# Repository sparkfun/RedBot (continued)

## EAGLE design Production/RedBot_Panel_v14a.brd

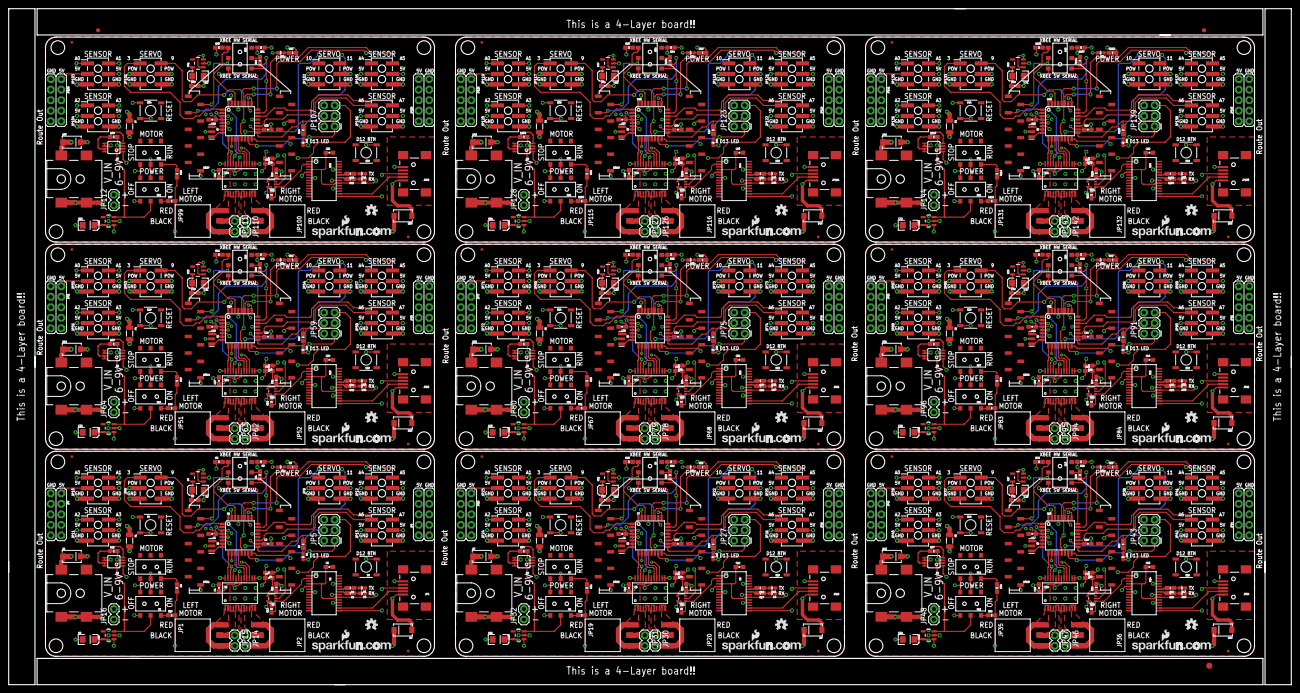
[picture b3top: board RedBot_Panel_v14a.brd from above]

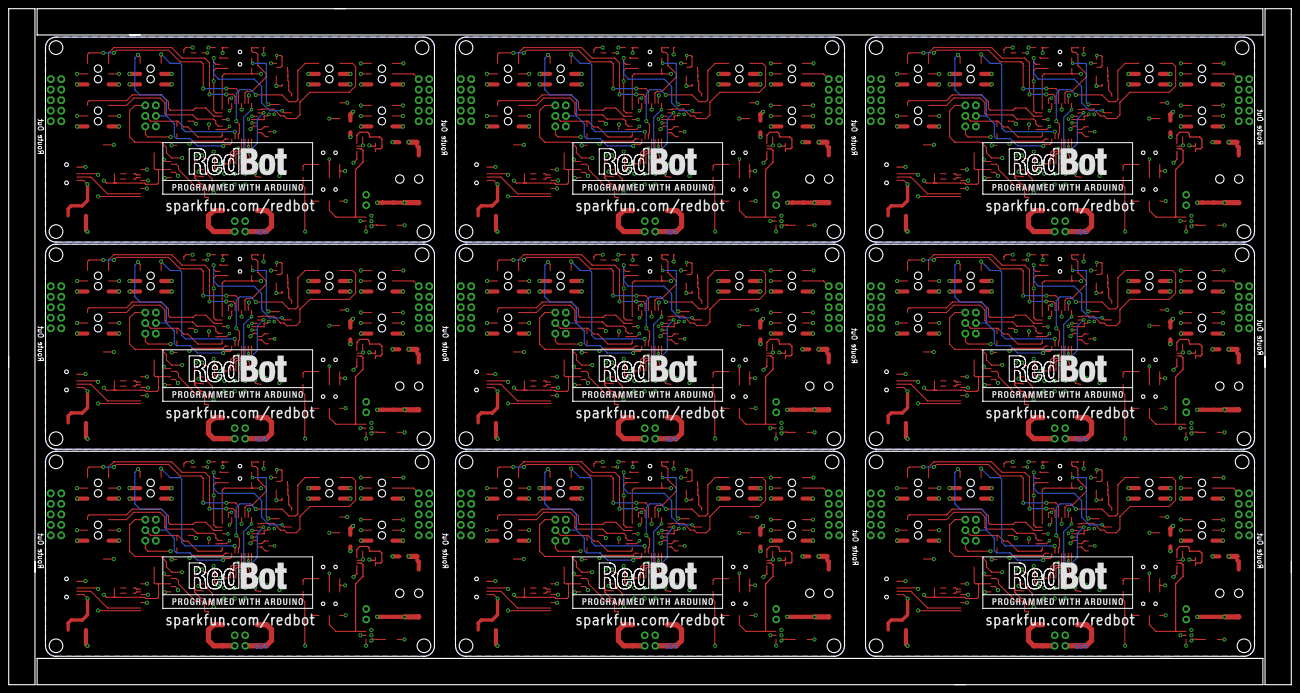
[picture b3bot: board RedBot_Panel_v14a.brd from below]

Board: 4 copper layers, 309.9 x 163.3 mm, 606 parts (9 on the bottom side), 531 nets.

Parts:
C1, C2, C3, C4, C5, C6, C7, C10, C11, C12, C13, C14, C17, C18, C19, C20, C21, C22, C25, C26, C27, C28, C29, C30, C33, C34, C35, C36, C37, C38, C41, C42, C43, C44, C45, C46, C49, C50, C51, C52, C53, C54, C57, C58, C59, C60, C61, C62, C65, C66, C67, C68, C69, C70: 0.1uF; 0603-CAP
C8, C9, C15, C16, C23, C24, C31, C32, C39, C40, C47, C48, C55, C56, C63, C64, C71, C72: 10uF; EIA3216
D1, D2, D7, D8, D13, D14, D19, D20, D25, D26, D31, D32, D37, D38, D43, D44, D49, D50: SMA-DIODE
D3, D4, D5, D6, D9, D10, D11, D12, D15, D16, D17, D18, D21, D22, D23, D24, D27, D28, D29, D30, D33, D34, D35, D36, D39, D40, D41, D42, D45, D46, D47, D48, D51, D52, D53, D54: GREEN; LED-0603
E$1: FIDUCIAL-1.5X3
E$7, E$8: FIDUCIAL-1X2
F1, F2, F3, F4, F5, F6, F7, F8, F9: PTCSMD; PTC-1206
FID1, FID2, FID3, FID4, FID5, FID6, FID7, FID8, FID9, FID10, FID11, FID12, FID13, FID14, FID15, FID16, FID17, FID18: FIDUCIALUFIDUCIAL; MICRO-FIDUCIAL
JP1, JP2, JP19, JP20, JP35, JP36, JP51, JP52, JP67, JP68, JP83, JP84, JP99, JP100, JP115, JP116, JP131, JP132: 1x3 RA Female .1"; 1X03_SMD_RA_FEMALE
JP3, JP17, JP33, JP49, JP65, JP81, JP97, JP113, JP129: 5.5x2.1mm Barrel; POWER_JACK_SMD
JP4, JP18, JP34, JP50, JP66, JP82, JP98, JP114, JP130: USB-B; USB-MINIB
JP5, JP27, JP43, JP59, JP75, JP91, JP107, JP123, JP139: AVR_SPI_PRG_6PTH; 2X3
JP6, JP7, JP28, JP29, JP44, JP45, JP60, JP61, JP76, JP77, JP92, JP93, JP108, JP109, JP124, JP125, JP140, JP141: M05X2NO_SILK; 2X5_NOSILK
JP8, JP9, JP10, JP11, JP12, JP13, JP21, JP22, JP23, JP24, JP25, JP26, JP37, JP38, JP39, JP40, JP41, JP42, JP53, JP54, JP55, JP56, JP57, JP58, JP69, JP70, JP71, JP72, JP73, JP74, JP85, JP86, JP87, JP88, JP89, JP90, JP101, JP102, JP103, JP104, JP105, JP106, JP117, JP118, JP119, JP120, JP121, JP122, JP133, JP134, JP135, JP136, JP137, JP138: 2X3_SMT_POSTS
JP14, JP15, JP16, JP30, JP31, JP32, JP46, JP47, JP48, JP62, JP63, JP64, JP78, JP79, JP80, JP94, JP95, JP96, JP110, JP111, JP112, JP126, JP127, JP128, JP142, JP143, JP144: 1X02
MOD1, MOD2, MOD3, MOD4, MOD5, MOD6, MOD7, MOD8, MOD9: XBEE-1B3; XBEE-SMD
Q1, Q2, Q3, Q4, Q5, Q6, Q7, Q8, Q9: MSOP8
R1, R9, R10, R11, R12, R13, R14, R21, R22, R24, R25, R26, R27, R34, R35, R37, R38, R39, R40, R47, R48, R50, R51, R52, R53, R60, R61, R63, R64, R65, R66, R73, R74, R76, R77, R78, R79, R86, R87, R89, R90, R91, R92, R99, R100, R102, R103, R104, R105, R112, R113, R115, R116, R117: 10k; 0603-RES
R2, R3, R4, R5, R6, R7, R8, R15, R16, R17, R18, R19, R20, R23, R28, R29, R30, R31, R32, R33, R36, R41, R42, R43, R44, R45, R46, R49, R54, R55, R56, R57, R58, R59, R62, R67, R68, R69, R70, R71, R72, R75, R80, R81, R82, R83, R84, R85, R88, R93, R94, R95, R96, R97, R98, R101, R106, R107, R108, R109, R110, R111, R114: 1k; 0603-RES
S1, S2, S3, S6, S7, S8, S11, S12, S13, S16, S17, S18, S21, S22, S23, S26, S27, S28, S31, S32, S33, S36, S37, S38, S41, S42, S43: DPDT; AYZ0202
S4, S5, S9, S10, S14, S15, S19, S20, S24, S25, S29, S30, S34, S35, S39, S40, S44, S45: TACTILE_SWITCH_SMD
SFE-LOGO1, SFE-LOGO2, SFE-LOGO3, SFE-LOGO4, SFE-LOGO5, SFE-LOGO6, SFE-LOGO7, SFE-LOGO8, SFE-LOGO9: LOGO-SFENEW; SFE-NEW-WEBLOGO
STANDOFF1, STANDOFF2, STANDOFF3, STANDOFF4, STANDOFF5, STANDOFF6, STANDOFF7, STANDOFF8, STANDOFF9, STANDOFF10, STANDOFF11, STANDOFF12, STANDOFF13, STANDOFF14, STANDOFF15, STANDOFF16, STANDOFF17, STANDOFF18, STANDOFF19, STANDOFF20, STANDOFF21, STANDOFF22, STANDOFF23, STANDOFF24, STANDOFF25, STANDOFF26, STANDOFF27, STANDOFF28, STANDOFF29, STANDOFF30, STANDOFF31, STANDOFF32, STANDOFF33, STANDOFF34, STANDOFF35, STANDOFF36: STAND-OFF
U1, U7, U13, U19, U25, U31, U37, U43, U49: ATMEGA328P; TQFP32-08
U2, U9, U15, U21, U27, U33, U39, U45, U51: TB6612FNG; SSOP24
U3, U10, U16, U22, U28, U34, U40, U46, U52: MIC5219 5V; SOT23-5
U4, U11, U17, U23, U29, U35, U41, U47, U53: MIC5219 3.3V; SOT23-5
U5, U8, U14, U20, U26, U32, U38, U44, U50: FT232RLSSOP; SSOP28DB
U6, U12, U18, U24, U30, U36, U42, U48, U54: 7408SE; SOT353
U$1, U$3, U$5, U$7, U$9, U$11, U$13, U$15, U$17: OSHW-LOGOS; OSHW-LOGO-S
U$2, U$4, U$6, U$8, U$10, U$12, U$14, U$16, U$23: REDBOT_LOGO
Y1, Y2, Y3, Y4, Y5, Y6, Y7, Y8, Y9: 16MHz; RESONATOR-SMD

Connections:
3.3V: C6.1, C8.A, MOD1.1, U4.5
3.3V1: C13.1, C15.A, MOD2.1, U11.5
3.3V2: C21.1, C23.A, MOD3.1, U17.5
3.3V3: C29.1, C31.A, MOD4.1, U23.5
3.3V4: C37.1, C39.A, MOD5.1, U29.5
3.3V5: C45.1, C47.A, MOD6.1, U35.5
3.3V6: C53.1, C55.A, MOD7.1, U41.5
3.3V7: C61.1, C63.A, MOD8.1, U47.5
3.3V8: C69.1, C71.A, MOD9.1, U53.5
5V: C2.1, C3.1, C4.1, C9.A, JP5.2, JP6.1, JP6.3, JP6.5, JP6.7, JP6.9, JP7.1, JP7.3, JP7.5, JP7.7, JP7.9, JP10.3, JP10.4, JP11.3, JP11.4, JP12.3, JP12.4, JP13.3, JP13.4, R1.1, R8.2, R12.2, R13.2, U1.4, U1.6, U1.18, U2.20, U3.5, U4.1, U4.3, U6.5
5V1: C1.1, C10.1, C11.1, C16.A, JP23.3, JP23.4, JP24.3, JP24.4, JP25.3, JP25.4, JP26.3, JP26.4, JP27.2, JP28.1, JP28.3, JP28.5, JP28.7, JP28.9, JP29.1, JP29.3, JP29.5, JP29.7, JP29.9, R14.1, R20.2, R25.2, R26.2, U7.4, U7.6, U7.18, U9.20, U10.5, U11.1, U11.3, U12.5
5V2: C17.1, C18.1, C19.1, C24.A, JP39.3, JP39.4, JP40.3, JP40.4, JP41.3, JP41.4, JP42.3, JP42.4, JP43.2, JP44.1, JP44.3, JP44.5, JP44.7, JP44.9, JP45.1, JP45.3, JP45.5, JP45.7, JP45.9, R27.1, R33.2, R38.2, R39.2, U13.4, U13.6, U13.18, U15.20, U16.5, U17.1, U17.3, U18.5
5V3: C25.1, C26.1, C27.1, C32.A, JP55.3, JP55.4, JP56.3, JP56.4, JP57.3, JP57.4, JP58.3, JP58.4, JP59.2, JP60.1, JP60.3, JP60.5, JP60.7, JP60.9, JP61.1, JP61.3, JP61.5, JP61.7, JP61.9, R40.1, R46.2, R51.2, R52.2, U19.4, U19.6, U19.18, U21.20, U22.5, U23.1, U23.3, U24.5
5V4: C33.1, C34.1, C35.1, C40.A, JP71.3, JP71.4, JP72.3, JP72.4, JP73.3, JP73.4, JP74.3, JP74.4, JP75.2, JP76.1, JP76.3, JP76.5, JP76.7, JP76.9, JP77.1, JP77.3, JP77.5, JP77.7, JP77.9, R53.1, R59.2, R64.2, R65.2, U25.4, U25.6, U25.18, U27.20, U28.5, U29.1, U29.3, U30.5
5V5: C41.1, C42.1, C43.1, C48.A, JP87.3, JP87.4, JP88.3, JP88.4, JP89.3, JP89.4, JP90.3, JP90.4, JP91.2, JP92.1, JP92.3, JP92.5, JP92.7, JP92.9, JP93.1, JP93.3, JP93.5, JP93.7, JP93.9, R66.1, R72.2, R77.2, R78.2, U31.4, U31.6, U31.18, U33.20, U34.5, U35.1, U35.3, U36.5
5V6: C49.1, C50.1, C51.1, C56.A, JP103.3, JP103.4, JP104.3, JP104.4, JP105.3, JP105.4, JP106.3, JP106.4, JP107.2, JP108.1, JP108.3, JP108.5, JP108.7, JP108.9, JP109.1, JP109.3, JP109.5, JP109.7, JP109.9, R79.1, R85.2, R90.2, R91.2, U37.4, U37.6, U37.18, U39.20, U40.5, U41.1, U41.3, U42.5
5V7: C57.1, C58.1, C59.1, C64.A, JP119.3, JP119.4, JP120.3, JP120.4, JP121.3, JP121.4, JP122.3, JP122.4, JP123.2, JP124.1, JP124.3, JP124.5, JP124.7, JP124.9, JP125.1, JP125.3, JP125.5, JP125.7, JP125.9, R92.1, R98.2, R103.2, R104.2, U43.4, U43.6, U43.18, U45.20, U46.5, U47.1, U47.3, U48.5
5V8: C65.1, C66.1, C67.1, C72.A, JP135.3, JP135.4, JP136.3, JP136.4, JP137.3, JP137.4, JP138.3, JP138.4, JP139.2, JP140.1, JP140.3, JP140.5, JP140.7, JP140.9, JP141.1, JP141.3, JP141.5, JP141.7, JP141.9, R105.1, R111.2, R116.2, R117.2, U49.4, U49.6, U49.18, U51.20, U52.5, U53.1, U53.3, U54.5
FT232_RXI: R3.1, U5.5
FT232_RXI1: R16.1, U8.5
FT232_RXI2: R29.1, U14.5
FT232_RXI3: R42.1, U20.5
FT232_RXI4: R55.1, U26.5
FT232_RXI5: R68.1, U32.5
FT232_RXI6: R81.1, U38.5
FT232_RXI7: R94.1, U44.5
FT232_RXI8: R107.1, U50.5
FT232_TXO: R2.1, U5.1
FT232_TXO1: R15.1, U8.1
FT232_TXO2: R28.1, U14.1
FT232_TXO3: R41.1, U20.1
FT232_TXO4: R54.1, U26.1
FT232_TXO5: R67.1, U32.1
FT232_TXO6: R80.1, U38.1
FT232_TXO7: R93.1, U44.1
FT232_TXO8: R106.1, U50.1
FTDI_DTR: R13.1, U5.2, U6.1
FTDI_DTR1: R26.1, U8.2, U12.1
FTDI_DTR2: R39.1, U14.2, U18.1
FTDI_DTR3: R52.1, U20.2, U24.1
FTDI_DTR4: R65.1, U26.2, U30.1
FTDI_DTR5: R78.1, U32.2, U36.1
FTDI_DTR6: R91.1, U38.2, U42.1
FTDI_DTR7: R104.1, U44.2, U48.1
FTDI_DTR8: R117.1, U50.2, U54.1
GND: C2.2, C3.2, C4.2, C5.2, C6.2, C8.C, C9.C, D4.C, D6.C, JP3.GND, JP3.P$4, JP4.GND, JP5.6, JP6.2, JP6.4, JP6.6, JP6.8, JP6.10, JP7.2, JP7.4, JP7.6, JP7.8, JP7.10, JP8.5, JP8.6, JP9.5, JP9.6, JP10.5, JP10.6, JP11.5, JP11.6, JP12.5, JP12.6, JP13.5, JP13.6, JP16.1, MOD1.10, Q1.1, S1.3, S1.6, S2.3, S4.1, S5.1, U1.3, U1.5, U1.21, U2.3, U2.4, U2.9, U2.10, U2.18, U3.2, U4.2, U5.7, U5.18, U5.21, U5.25, U5.26, U6.3, Y1.2
GND1: C1.2, C10.2, C11.2, C12.2, C13.2, C15.C, C16.C, D10.C, D12.C, JP17.GND, JP17.P$4, JP18.GND, JP21.5, JP21.6, JP22.5, JP22.6, JP23.5, JP23.6, JP24.5, JP24.6, JP25.5, JP25.6, JP26.5, JP26.6, JP27.6, JP28.2, JP28.4, JP28.6, JP28.8, JP28.10, JP29.2, JP29.4, JP29.6, JP29.8, JP29.10, JP32.1, MOD2.10, Q2.1, S6.3, S6.6, S7.3, S9.1, S10.1, U7.3, U7.5, U7.21, U8.7, U8.18, U8.21, U8.25, U8.26, U9.3, U9.4, U9.9, U9.10, U9.18, U10.2, U11.2, U12.3, Y2.2
GND2: C17.2, C18.2, C19.2, C20.2, C21.2, C23.C, C24.C, D16.C, D18.C, JP33.GND, JP33.P$4, JP34.GND, JP37.5, JP37.6, JP38.5, JP38.6, JP39.5, JP39.6, JP40.5, JP40.6, JP41.5, JP41.6, JP42.5, JP42.6, JP43.6, JP44.2, JP44.4, JP44.6, JP44.8, JP44.10, JP45.2, JP45.4, JP45.6, JP45.8, JP45.10, JP48.1, MOD3.10, Q3.1, S11.3, S11.6, S12.3, S14.1, S15.1, U13.3, U13.5, U13.21, U14.7, U14.18, U14.21, U14.25, U14.26, U15.3, U15.4, U15.9, U15.10, U15.18, U16.2, U17.2, U18.3, Y3.2
GND3: C25.2, C26.2, C27.2, C28.2, C29.2, C31.C, C32.C, D22.C, D24.C, JP49.GND, JP49.P$4, JP50.GND, JP53.5, JP53.6, JP54.5, JP54.6, JP55.5, JP55.6, JP56.5, JP56.6, JP57.5, JP57.6, JP58.5, JP58.6, JP59.6, JP60.2, JP60.4, JP60.6, JP60.8, JP60.10, JP61.2, JP61.4, JP61.6, JP61.8, JP61.10, JP64.1, MOD4.10, Q4.1, S16.3, S16.6, S17.3, S19.1, S20.1, U19.3, U19.5, U19.21, U20.7, U20.18, U20.21, U20.25, U20.26, U21.3, U21.4, U21.9, U21.10, U21.18, U22.2, U23.2, U24.3, Y4.2
GND4: C33.2, C34.2, C35.2, C36.2, C37.2, C39.C, C40.C, D28.C, D30.C, JP65.GND, JP65.P$4, JP66.GND, JP69.5, JP69.6, JP70.5, JP70.6, JP71.5, JP71.6, JP72.5, JP72.6, JP73.5, JP73.6, JP74.5, JP74.6, JP75.6, JP76.2, JP76.4, JP76.6, JP76.8, JP76.10, JP77.2, JP77.4, JP77.6, JP77.8, JP77.10, JP80.1, MOD5.10, Q5.1, S21.3, S21.6, S22.3, S24.1, S25.1, U25.3, U25.5, U25.21, U26.7, U26.18, U26.21, U26.25, U26.26, U27.3, U27.4, U27.9, U27.10, U27.18, U28.2, U29.2, U30.3, Y5.2
GND5: C41.2, C42.2, C43.2, C44.2, C45.2, C47.C, C48.C, D34.C, D36.C, JP81.GND, JP81.P$4, JP82.GND, JP85.5, JP85.6, JP86.5, JP86.6, JP87.5, JP87.6, JP88.5, JP88.6, JP89.5, JP89.6, JP90.5, JP90.6, JP91.6, JP92.2, JP92.4, JP92.6, JP92.8, JP92.10, JP93.2, JP93.4, JP93.6, JP93.8, JP93.10, JP96.1, MOD6.10, Q6.1, S26.3, S26.6, S27.3, S29.1, S30.1, U31.3, U31.5, U31.21, U32.7, U32.18, U32.21, U32.25, U32.26, U33.3, U33.4, U33.9, U33.10, U33.18, U34.2, U35.2, U36.3, Y6.2
GND6: C49.2, C50.2, C51.2, C52.2, C53.2, C55.C, C56.C, D40.C, D42.C, JP97.GND, JP97.P$4, JP98.GND, JP101.5, JP101.6, JP102.5, JP102.6, JP103.5, JP103.6, JP104.5, JP104.6, JP105.5, JP105.6, JP106.5, JP106.6, JP107.6, JP108.2, JP108.4, JP108.6, JP108.8, JP108.10, JP109.2, JP109.4, JP109.6, JP109.8, JP109.10, JP112.1, MOD7.10, Q7.1, S31.3, S31.6, S32.3, S34.1, S35.1, U37.3, U37.5, U37.21, U38.7, U38.18, U38.21, U38.25, U38.26, U39.3, U39.4, U39.9, U39.10, U39.18, U40.2, U41.2, U42.3, Y7.2
GND7: C57.2, C58.2, C59.2, C60.2, C61.2, C63.C, C64.C, D46.C, D48.C, JP113.GND, JP113.P$4, JP114.GND, JP117.5, JP117.6, JP118.5, JP118.6, JP119.5, JP119.6, JP120.5, JP120.6, JP121.5, JP121.6, JP122.5, JP122.6, JP123.6, JP124.2, JP124.4, JP124.6, JP124.8, JP124.10, JP125.2, JP125.4, JP125.6, JP125.8, JP125.10, JP128.1, MOD8.10, Q8.1, S36.3, S36.6, S37.3, S39.1, S40.1, U43.3, U43.5, U43.21, U44.7, U44.18, U44.21, U44.25, U44.26, U45.3, U45.4, U45.9, U45.10, U45.18, U46.2, U47.2, U48.3, Y8.2
GND8: C65.2, C66.2, C67.2, C68.2, C69.2, C71.C, C72.C, D52.C, D54.C, JP129.GND, JP129.P$4, JP130.GND, JP133.5, JP133.6, JP134.5, JP134.6, JP135.5, JP135.6, JP136.5, JP136.6, JP137.5, JP137.6, JP138.5, JP138.6, JP139.6, JP140.2, JP140.4, JP140.6, JP140.8, JP140.10, JP141.2, JP141.4, JP141.6, JP141.8, JP141.10, JP144.1, MOD9.10, Q9.1, S41.3, S41.6, S42.3, S44.1, S45.1, U49.3, U49.5, U49.21, U50.7, U50.18, U50.21, U50.25, U50.26, U51.3, U51.4, U51.9, U51.10, U51.18, U52.2, U53.2, U54.3, Y9.2
L01: JP1.1, JP1.3, JP15.2, U2.1, U2.2
L02: JP1.2, JP15.1, U2.5, U2.6
L03: JP19.1, JP19.3, JP31.2, U9.1, U9.2
L04: JP19.2, JP31.1, U9.5, U9.6
L05: JP35.1, JP35.3, JP47.2, U15.1, U15.2
L06: JP35.2, JP47.1, U15.5, U15.6
L07: JP51.1, JP51.3, JP63.2, U21.1, U21.2
L08: JP51.2, JP63.1, U21.5, U21.6
L09: JP67.1, JP67.3, JP79.2, U27.1, U27.2
L10: JP67.2, JP79.1, U27.5, U27.6
L11: JP83.1, JP83.3, JP95.2, U33.1, U33.2
L12: JP83.2, JP95.1, U33.5, U33.6
L13: JP99.1, JP99.3, JP111.2, U39.1, U39.2
L14: JP99.2, JP111.1, U39.5, U39.6
L15: JP115.1, JP115.3, JP127.2, U45.1, U45.2
L16: JP115.2, JP127.1, U45.5, U45.6
L17: JP131.1, JP131.3, JP143.2, U51.1, U51.2
L18: JP131.2, JP143.1, U51.5, U51.6
L_CTRL_1: U1.32, U2.21
L_CTRL_2: U1.2, U2.22
L_CTRL_3: U7.2, U9.22
L_CTRL_4: U7.32, U9.21
L_CTRL_5: U13.2, U15.22
L_CTRL_6: U13.32, U15.21
L_CTRL_7: U19.2, U21.22
L_CTRL_8: U19.32, U21.21
L_CTRL_9: U25.2, U27.22
L_CTRL_10: U25.32, U27.21
L_CTRL_11: U31.2, U33.22
L_CTRL_12: U31.32, U33.21
L_CTRL_13: U37.2, U39.22
L_CTRL_14: U37.32, U39.21
L_CTRL_15: U43.2, U45.22
L_CTRL_16: U43.32, U45.21
L_CTRL_17: U49.2, U51.22
L_CTRL_18: U49.32, U51.21
MISO: JP5.1, S5.3, U1.16
MISO1: JP27.1, S10.3, U7.16
MISO2: JP43.1, S15.3, U13.16
MISO3: JP59.1, S20.3, U19.16
MISO4: JP75.1, S25.3, U25.16
MISO5: JP91.1, S30.3, U31.16
MISO6: JP107.1, S35.3, U37.16
MISO7: JP123.1, S40.3, U43.16
MISO8: JP139.1, S45.3, U49.16
MOTOR_ENABLE: S1.5, S2.2, U2.19
MOTOR_ENABLE1: S6.5, S7.2, U9.19
MOTOR_ENABLE2: S11.5, S12.2, U15.19
MOTOR_ENABLE3: S16.5, S17.2, U21.19
MOTOR_ENABLE4: S21.5, S22.2, U27.19
MOTOR_ENABLE5: S26.5, S27.2, U33.19
MOTOR_ENABLE6: S31.5, S32.2, U39.19
MOTOR_ENABLE7: S36.5, S37.2, U45.19
MOTOR_ENABLE8: S41.5, S42.2, U51.19
unnamed: R4.2, S3.2
unnamed: Q1.4, Q1.7, Q1.8, R11.1
unnamed: D5.C, R6.1
unnamed: D3.C, R5.1
unnamed: C7.2, U6.4
unnamed: JP4.MTN1, JP4.MTN2, JP4.MTN3, JP4.MTN4
unnamed: D4.A, R7.1
unnamed: D6.A, R8.1
unnamed: F1.2, Q1.5, Q1.6
unnamed: JP18.D-, U8.16
unnamed: JP18.D+, U8.15
unnamed: U7.8, Y2.3
unnamed: U7.7, Y2.1
unnamed: D10.A, R19.1
unnamed: D12.A, R20.1
unnamed: R21.1, S7.1
unnamed: C14.2, U12.4
unnamed: R9.1, S2.1
unnamed: R23.2, S8.2
unnamed: JP18.MTN1, JP18.MTN2, JP18.MTN3, JP18.MTN4
unnamed: Q2.4, Q2.7, Q2.8, R24.1
unnamed: D11.C, R18.1
unnamed: U1.8, Y1.3
unnamed: U1.7, Y1.1
unnamed: D9.C, R17.1
unnamed: JP4.D-, U5.16
unnamed: JP4.D+, U5.15
unnamed: F2.2, Q2.5, Q2.6
unnamed: JP34.D-, U14.16
unnamed: JP34.D+, U14.15
unnamed: U13.8, Y3.3
unnamed: U13.7, Y3.1
unnamed: D16.A, R32.1
unnamed: D18.A, R33.1
unnamed: R34.1, S12.1
unnamed: C22.2, U18.4
unnamed: R36.2, S13.2
unnamed: JP34.MTN1, JP34.MTN2, JP34.MTN3, JP34.MTN4
unnamed: Q3.4, Q3.7, Q3.8, R37.1
unnamed: D17.C, R31.1
unnamed: D15.C, R30.1
unnamed: F3.2, Q3.5, Q3.6
unnamed: JP50.D-, U20.16
unnamed: JP50.D+, U20.15
unnamed: U19.8, Y4.3
unnamed: U19.7, Y4.1
unnamed: D22.A, R45.1
unnamed: D24.A, R46.1
unnamed: R47.1, S17.1
unnamed: C30.2, U24.4
unnamed: R49.2, S18.2
unnamed: JP50.MTN1, JP50.MTN2, JP50.MTN3, JP50.MTN4
unnamed: Q4.4, Q4.7, Q4.8, R50.1
unnamed: D23.C, R44.1
unnamed: D21.C, R43.1
unnamed: F4.2, Q4.5, Q4.6
unnamed: JP66.D-, U26.16
unnamed: JP66.D+, U26.15
unnamed: U25.8, Y5.3
unnamed: U25.7, Y5.1
unnamed: D28.A, R58.1
unnamed: D30.A, R59.1
unnamed: R60.1, S22.1
unnamed: C38.2, U30.4
unnamed: R62.2, S23.2
unnamed: JP66.MTN1, JP66.MTN2, JP66.MTN3, JP66.MTN4
unnamed: Q5.4, Q5.7, Q5.8, R63.1
unnamed: D29.C, R57.1
unnamed: D27.C, R56.1
unnamed: F5.2, Q5.5, Q5.6
unnamed: JP82.D-, U32.16
unnamed: JP82.D+, U32.15
unnamed: U31.8, Y6.3
unnamed: U31.7, Y6.1
unnamed: D34.A, R71.1
unnamed: D36.A, R72.1
unnamed: R73.1, S27.1
unnamed: C46.2, U36.4
unnamed: R75.2, S28.2
unnamed: JP82.MTN1, JP82.MTN2, JP82.MTN3, JP82.MTN4
unnamed: Q6.4, Q6.7, Q6.8, R76.1
unnamed: D35.C, R70.1
unnamed: D33.C, R69.1
unnamed: F6.2, Q6.5, Q6.6
unnamed: JP98.D-, U38.16
unnamed: JP98.D+, U38.15
unnamed: U37.8, Y7.3
unnamed: U37.7, Y7.1
unnamed: D40.A, R84.1
unnamed: D42.A, R85.1
unnamed: R86.1, S32.1
unnamed: C54.2, U42.4
unnamed: R88.2, S33.2
unnamed: JP98.MTN1, JP98.MTN2, JP98.MTN3, JP98.MTN4
unnamed: Q7.4, Q7.7, Q7.8, R89.1
unnamed: D41.C, R83.1
unnamed: D39.C, R82.1
unnamed: F7.2, Q7.5, Q7.6
unnamed: JP114.D-, U44.16
unnamed: JP114.D+, U44.15
unnamed: U43.8, Y8.3
unnamed: U43.7, Y8.1
unnamed: D46.A, R97.1
unnamed: D48.A, R98.1
unnamed: R99.1, S37.1
unnamed: C62.2, U48.4
unnamed: R101.2, S38.2
unnamed: JP114.MTN1, JP114.MTN2, JP114.MTN3, JP114.MTN4
unnamed: Q8.4, Q8.7, Q8.8, R102.1
unnamed: D47.C, R96.1
unnamed: D45.C, R95.1
unnamed: F8.2, Q8.5, Q8.6
unnamed: JP130.D-, U50.16
unnamed: JP130.D+, U50.15
unnamed: U49.8, Y9.3
unnamed: U49.7, Y9.1
unnamed: D52.A, R110.1
unnamed: D54.A, R111.1
unnamed: R112.1, S42.1
unnamed: C70.2, U54.4
unnamed: R114.2, S43.2
unnamed: JP130.MTN1, JP130.MTN2, JP130.MTN3, JP130.MTN4
unnamed: Q9.4, Q9.7, Q9.8, R115.1
unnamed: D53.C, R109.1
unnamed: D51.C, R108.1
unnamed: F9.2, Q9.5, Q9.6
PG_EN: R10.1, S1.1
PG_EN1: R22.1, S6.1
PG_EN2: R35.1, S11.1
PG_EN3: R48.1, S16.1
PG_EN4: R61.1, S21.1
PG_EN5: R74.1, S26.1
PG_EN6: R87.1, S31.1
PG_EN7: R100.1, S36.1
PG_EN8: R113.1, S41.1
PROGRAM_ENABLE: Q1.2, S1.2, U3.3
PROGRAM_ENABLE1: Q2.2, S6.2, U10.3
PROGRAM_ENABLE2: Q3.2, S11.2, U16.3
PROGRAM_ENABLE3: Q4.2, S16.2, U22.3
PROGRAM_ENABLE4: Q5.2, S21.2, U28.3
PROGRAM_ENABLE5: Q6.2, S26.2, U34.3
PROGRAM_ENABLE6: Q7.2, S31.2, U40.3
PROGRAM_ENABLE7: Q8.2, S36.2, U46.3
PROGRAM_ENABLE8: Q9.2, S41.2, U52.3
PWML: U1.9, U2.23
PWML1: U7.9, U9.23
PWML2: U13.9, U15.23
PWML3: U19.9, U21.23
PWML4: U25.9, U27.23
PWML5: U31.9, U33.23
PWML6: U37.9, U39.23
PWML7: U43.9, U45.23
PWML8: U49.9, U51.23
PWMR: U1.10, U2.15
PWMR1: U7.10, U9.15
PWMR2: U13.10, U15.15
PWMR3: U19.10, U21.15
PWMR4: U25.10, U27.15
PWMR5: U31.10, U33.15
PWMR6: U37.10, U39.15
PWMR7: U43.10, U45.15
PWMR8: U49.10, U51.15
R01: JP2.1, JP2.3, JP14.2, U2.11, U2.12
R02: JP2.2, JP14.1, U2.7, U2.8
R03: JP20.2, JP30.1, U9.7, U9.8
R04: JP20.1, JP20.3, JP30.2, U9.11, U9.12
R05: JP36.2, JP46.1, U15.7, U15.8
R06: JP36.1, JP36.3, JP46.2, U15.11, U15.12
R07: JP52.2, JP62.1, U21.7, U21.8
R08: JP52.1, JP52.3, JP62.2, U21.11, U21.12
R09: JP68.2, JP78.1, U27.7, U27.8
R10: JP68.1, JP68.3, JP78.2, U27.11, U27.12
R11: JP84.2, JP94.1, U33.7, U33.8
R12: JP84.1, JP84.3, JP94.2, U33.11, U33.12
R13: JP100.2, JP110.1, U39.7, U39.8
R14: JP100.1, JP100.3, JP110.2, U39.11, U39.12
R15: JP116.2, JP126.1, U45.7, U45.8
R16: JP116.1, JP116.3, JP126.2, U45.11, U45.12
R17: JP132.2, JP142.1, U51.7, U51.8
R18: JP132.1, JP132.3, JP142.2, U51.11, U51.12
RESET: C7.1, JP5.5, R1.2, S4.3, U1.29
RESET1: C14.1, JP27.5, R14.2, S9.3, U7.29
RESET2: C22.1, JP43.5, R27.2, S14.3, U13.29
RESET3: C30.1, JP59.5, R40.2, S19.3, U19.29
RESET4: C38.1, JP75.5, R53.2, S24.3, U25.29
RESET5: C46.1, JP91.5, R66.2, S29.3, U31.29
RESET6: C54.1, JP107.5, R79.2, S34.3, U37.29
RESET7: C62.1, JP123.5, R92.2, S39.3, U43.29
RESET8: C70.1, JP139.5, R105.2, S44.3, U49.29
RXI: R2.2, S3.4, U1.30
RXI1: R15.2, S8.4, U7.30
RXI2: R28.2, S13.4, U13.30
RXI3: R41.2, S18.4, U19.30
RXI4: R54.2, S23.4, U25.30
RXI5: R67.2, S28.4, U31.30
RXI6: R80.2, S33.4, U37.30
RXI7: R93.2, S38.4, U43.30
RXI8: R106.2, S43.4, U49.30
RXLED: R5.2, U5.22
RXLED1: R17.2, U8.22
RXLED2: R30.2, U14.22
RXLED3: R43.2, U20.22
RXLED4: R56.2, U26.22
RXLED5: R69.2, U32.22
RXLED6: R82.2, U38.22
RXLED7: R95.2, U44.22
RXLED8: R108.2, U50.22
R_CTRL_1: U1.11, U2.17
R_CTRL_2: U1.12, U2.16
R_CTRL_3: U7.11, U9.17
R_CTRL_4: U7.12, U9.16
R_CTRL_5: U13.11, U15.17
R_CTRL_6: U13.12, U15.16
R_CTRL_7: U19.11, U21.17
R_CTRL_8: U19.12, U21.16
R_CTRL_9: U25.11, U27.17
R_CTRL_10: U25.12, U27.16
R_CTRL_11: U31.11, U33.17
R_CTRL_12: U31.12, U33.16
R_CTRL_13: U37.11, U39.17
R_CTRL_14: U37.12, U39.16
R_CTRL_15: U43.11, U45.17
R_CTRL_16: U43.12, U45.16
R_CTRL_17: U49.11, U51.17
R_CTRL_18: U49.12, U51.16
SCK: JP5.3, R7.2, U1.17
SCK1: JP27.3, R19.2, U7.17
SCK2: JP43.3, R32.2, U13.17
SCK3: JP59.3, R45.2, U19.17
SCK4: JP75.3, R58.2, U25.17
SCK5: JP91.3, R71.2, U31.17
SCK6: JP107.3, R84.2, U37.17
SCK7: JP123.3, R97.2, U43.17
SCK8: JP139.3, R110.2, U49.17
SENSOR_0/SW_TXO: JP10.1, S3.3, U1.23
SENSOR_0/SW_TXO1: JP23.1, S8.3, U7.23
SENSOR_0/SW_TXO2: JP39.1, S13.3, U13.23
SENSOR_0/SW_TXO3: JP55.1, S18.3, U19.23
SENSOR_0/SW_TXO4: JP71.1, S23.3, U25.23
SENSOR_0/SW_TXO5: JP87.1, S28.3, U31.23
SENSOR_0/SW_TXO6: JP103.1, S33.3, U37.23
SENSOR_0/SW_TXO7: JP119.1, S38.3, U43.23
SENSOR_0/SW_TXO8: JP135.1, S43.3, U49.23
SENSOR_1: JP24.1, U7.25
SENSOR_1/SW_RXI: JP10.2, S3.6, U1.24
SENSOR_1/SW_RXI1: JP23.2, S8.6, U7.24
SENSOR_1/SW_RXI2: JP39.2, S13.6, U13.24
SENSOR_1/SW_RXI3: JP55.2, S18.6, U19.24
SENSOR_1/SW_RXI4: JP71.2, S23.6, U25.24
SENSOR_1/SW_RXI5: JP87.2, S28.6, U31.24
SENSOR_1/SW_RXI6: JP103.2, S33.6, U37.24
SENSOR_1/SW_RXI7: JP119.2, S38.6, U43.24
SENSOR_1/SW_RXI8: JP135.2, S43.6, U49.24
SENSOR_2: JP11.1, U1.25
SENSOR_3: JP11.2, U1.26
SENSOR_4: JP12.1, U1.27
SENSOR_5: JP12.2, U1.28
SENSOR_6: JP13.1, U1.19
SENSOR_7: JP13.2, U1.22
SENSOR_8: JP24.2, U7.26
SENSOR_9: JP25.1, U7.27
SENSOR_10: JP25.2, U7.28
SENSOR_11: JP26.1, U7.19
SENSOR_12: JP26.2, U7.22
SENSOR_13: JP40.1, U13.25
SENSOR_14: JP40.2, U13.26
SENSOR_15: JP41.1, U13.27
SENSOR_16: JP41.2, U13.28
SENSOR_17: JP42.1, U13.19
SENSOR_18: JP42.2, U13.22
SENSOR_19: JP56.1, U19.25
SENSOR_20: JP56.2, U19.26
SENSOR_21: JP57.1, U19.27
SENSOR_22: JP57.2, U19.28
SENSOR_23: JP58.1, U19.19
SENSOR_24: JP58.2, U19.22
SENSOR_25: JP72.1, U25.25
SENSOR_26: JP72.2, U25.26
SENSOR_27: JP73.1, U25.27
SENSOR_28: JP73.2, U25.28
SENSOR_29: JP74.1, U25.19
SENSOR_30: JP74.2, U25.22
SENSOR_31: JP88.1, U31.25
SENSOR_32: JP88.2, U31.26
SENSOR_33: JP89.1, U31.27
SENSOR_34: JP89.2, U31.28
SENSOR_35: JP90.1, U31.19
SENSOR_36: JP90.2, U31.22
SENSOR_37: JP104.1, U37.25
SENSOR_38: JP104.2, U37.26
SENSOR_39: JP105.1, U37.27
SENSOR_40: JP105.2, U37.28
SENSOR_41: JP106.1, U37.19
SENSOR_42: JP106.2, U37.22
SENSOR_43: JP120.1, U43.25
SENSOR_44: JP120.2, U43.26
SENSOR_45: JP121.1, U43.27
SENSOR_46: JP121.2, U43.28
SENSOR_47: JP122.1, U43.19
SENSOR_48: JP122.2, U43.22
SENSOR_49: JP136.1, U49.25
SENSOR_50: JP136.2, U49.26
SENSOR_51: JP137.1, U49.27
SENSOR_52: JP137.2, U49.28
SENSOR_53: JP138.1, U49.19
SENSOR_54: JP138.2, U49.22
SERVO_1: JP8.1, U1.1
SERVO_2: JP8.2, U1.13
SERVO_3: JP9.1, U1.14
SERVO_4: JP21.1, U7.1
SERVO_4/MOSI: JP5.4, JP9.2, U1.15
SERVO_4/MOSI1: JP22.2, JP27.4, U7.15
SERVO_4/MOSI2: JP38.2, JP43.4, U13.15
SERVO_4/MOSI3: JP54.2, JP59.4, U19.15
SERVO_4/MOSI4: JP70.2, JP75.4, U25.15
SERVO_4/MOSI5: JP86.2, JP91.4, U31.15
SERVO_4/MOSI6: JP102.2, JP107.4, U37.15
SERVO_4/MOSI7: JP118.2, JP123.4, U43.15
SERVO_4/MOSI8: JP134.2, JP139.4, U49.15
SERVO_5: JP21.2, U7.13
SERVO_6: JP22.1, U7.14
SERVO_7: JP37.1, U13.1
SERVO_8: JP37.2, U13.13
SERVO_9: JP38.1, U13.14
SERVO_10: JP53.1, U19.1
SERVO_11: JP53.2, U19.13
SERVO_12: JP54.1, U19.14
SERVO_13: JP69.1, U25.1
SERVO_14: JP69.2, U25.13
SERVO_15: JP70.1, U25.14
SERVO_16: JP85.1, U31.1
SERVO_17: JP85.2, U31.13
SERVO_18: JP86.1, U31.14
SERVO_19: JP101.1, U37.1
SERVO_20: JP101.2, U37.13
SERVO_21: JP102.1, U37.14
SERVO_22: JP117.1, U43.1
SERVO_23: JP117.2, U43.13
SERVO_24: JP118.1, U43.14
SERVO_25: JP133.1, U49.1
SERVO_26: JP133.2, U49.13
SERVO_27: JP134.1, U49.14
TXLED: R6.2, U5.23
TXLED1: R18.2, U8.23
TXLED2: R31.2, U14.23
TXLED3: R44.2, U20.23
TXLED4: R57.2, U26.23
TXLED5: R70.2, U32.23
TXLED6: R83.2, U38.23
TXLED7: R96.2, U44.23
TXLED8: R109.2, U50.23
TXO: R3.2, S3.1, U1.31
TXO1: R16.2, S8.1, U7.31
TXO2: R29.2, S13.1, U13.31
TXO3: R42.2, S18.1, U19.31
TXO4: R55.2, S23.1, U25.31
TXO5: R68.2, S28.1, U31.31
TXO6: R81.2, S33.1, U37.31
TXO7: R94.2, S38.1, U43.31
TXO8: R107.2, S43.1, U49.31
V_BATT: D1.A, JP3.VIN0, JP16.2, Q1.3, R11.2, U2.13, U2.14, U2.24
V_BATT1: D7.A, JP17.VIN0, JP32.2, Q2.3, R24.2, U9.13, U9.14, U9.24
V_BATT2: D13.A, JP33.VIN0, JP48.2, Q3.3, R37.2, U15.13, U15.14, U15.24
V_BATT3: D19.A, JP49.VIN0, JP64.2, Q4.3, R50.2, U21.13, U21.14, U21.24
V_BATT4: D25.A, JP65.VIN0, JP80.2, Q5.3, R63.2, U27.13, U27.14, U27.24
V_BATT5: D31.A, JP81.VIN0, JP96.2, Q6.3, R76.2, U33.13, U33.14, U33.24
V_BATT6: D37.A, JP97.VIN0, JP112.2, Q7.3, R89.2, U39.13, U39.14, U39.24
V_BATT7: D43.A, JP113.VIN0, JP128.2, Q8.3, R102.2, U45.13, U45.14, U45.24
V_BATT8: D49.A, JP129.VIN0, JP144.2, Q9.3, R115.2, U51.13, U51.14, U51.24
V_GATED: F1.1, JP8.3, JP8.4, JP9.3, JP9.4
V_GATED1: F2.1, JP21.3, JP21.4, JP22.3, JP22.4
V_GATED2: F3.1, JP37.3, JP37.4, JP38.3, JP38.4
V_GATED3: F4.1, JP53.3, JP53.4, JP54.3, JP54.4
V_GATED4: F5.1, JP69.3, JP69.4, JP70.3, JP70.4
V_GATED5: F6.1, JP85.3, JP85.4, JP86.3, JP86.4
V_GATED6: F7.1, JP101.3, JP101.4, JP102.3, JP102.4
V_GATED7: F8.1, JP117.3, JP117.4, JP118.3, JP118.4
V_GATED8: F9.1, JP133.3, JP133.4, JP134.3, JP134.4
V_IN: D1.C, D2.C, R9.2, R10.2, U3.1
V_IN1: D7.C, D8.C, R21.2, R22.2, U10.1
V_IN2: D13.C, D14.C, R34.2, R35.2, U16.1
V_IN3: D19.C, D20.C, R47.2, R48.2, U22.1
V_IN4: D25.C, D26.C, R60.2, R61.2, U28.1
V_IN5: D31.C, D32.C, R73.2, R74.2, U34.1
V_IN6: D37.C, D38.C, R86.2, R87.2, U40.1
V_IN7: D43.C, D44.C, R99.2, R100.2, U46.1
V_IN8: D49.C, D50.C, R112.2, R113.2, U52.1
V_USB: C5.1, D2.A, D3.A, D5.A, JP4.VBUS, U5.4, U5.20
V_USB1: C12.1, D8.A, D9.A, D11.A, JP18.VBUS, U8.4, U8.20
V_USB2: C20.1, D14.A, D15.A, D17.A, JP34.VBUS, U14.4, U14.20
V_USB3: C28.1, D20.A, D21.A, D23.A, JP50.VBUS, U20.4, U20.20
V_USB4: C36.1, D26.A, D27.A, D29.A, JP66.VBUS, U26.4, U26.20
V_USB5: C44.1, D32.A, D33.A, D35.A, JP82.VBUS, U32.4, U32.20
V_USB6: C52.1, D38.A, D39.A, D41.A, JP98.VBUS, U38.4, U38.20
V_USB7: C60.1, D44.A, D45.A, D47.A, JP114.VBUS, U44.4, U44.20
V_USB8: C68.1, D50.A, D51.A, D53.A, JP130.VBUS, U50.4, U50.20
XBEE_DIO1: MOD2.17, R25.1, U12.2
XBEE_DIO2: MOD3.17, R38.1, U18.2
XBEE_DIO3: MOD1.17, R12.1, U6.2
XBEE_DIO4: MOD4.17, R51.1, U24.2
XBEE_DIO5: MOD5.17, R64.1, U30.2
XBEE_DIO6: MOD6.17, R77.1, U36.2
XBEE_DIO7: MOD7.17, R90.1, U42.2
XBEE_DIO8: MOD8.17, R103.1, U48.2
XBEE_DIO9: MOD9.17, R116.1, U54.2
XBEE_RXI: MOD1.3, R4.1
XBEE_RXI1: MOD2.3, R23.1
XBEE_RXI2: MOD3.3, R36.1
XBEE_RXI3: MOD4.3, R49.1
XBEE_RXI4: MOD5.3, R62.1
XBEE_RXI5: MOD6.3, R75.1
XBEE_RXI6: MOD7.3, R88.1
XBEE_RXI7: MOD8.3, R101.1
XBEE_RXI8: MOD9.3, R114.1
XBEE_TXO: MOD1.2, S3.5
XBEE_TXO1: MOD2.2, S8.5
XBEE_TXO2: MOD3.2, S13.5
XBEE_TXO3: MOD4.2, S18.5
XBEE_TXO4: MOD5.2, S23.5
XBEE_TXO5: MOD6.2, S28.5
XBEE_TXO6: MOD7.2, S33.5
XBEE_TXO7: MOD8.2, S38.5
XBEE_TXO8: MOD9.2, S43.5

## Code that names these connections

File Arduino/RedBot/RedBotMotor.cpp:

#include "RedBot.h"
#include <Arduino.h>

RedBotMotor::RedBotMotor()
{
  pinMode(R_CTRL_1, OUTPUT);
  pinMode(R_CTRL_2, OUTPUT);
  pinMode(L_CTRL_1, OUTPUT);
  pinMode(L_CTRL_2, OUTPUT);
}

void RedBotMotor::stop()
{
  leftStop();
  rightStop(); 
}

void RedBotMotor::brake()
{
  leftBrake();
  rightBrake(); 
}

void RedBotMotor::drive(int speed)
{
  if (speed > 0)
  {
    leftFwd((byte)(abs(speed)));
    rightFwd((byte)(abs(speed)));
  }
  else
  {
    leftRev((byte)(abs(speed)));
    rightRev((byte)(abs(speed)));
  }
}

void RedBotMotor::pivot(int speed)
{
  if (speed > 0)
  {
    leftRev((byte)(abs(speed)));
    rightFwd((byte)(abs(speed)));
  }
  else
  {
    leftFwd((byte)(abs(speed)));
    rightRev((byte)(abs(speed)));
  }
}

void RedBotMotor::rightDrive(int speed)
{
  if (speed > 0)
  {
    rightFwd((byte)(abs(speed)));
  }
  else
  {
    rightRev((byte)(abs(speed)));
  }
}

void RedBotMotor::leftDrive(int speed)
{
  if (speed > 0)
  {
    leftFwd((byte)(abs(speed)));
  }
  else
  {
    leftRev((byte)(abs(speed)));
  }
}

void RedBotMotor::leftBrake()
{
  digitalWrite(L_CTRL_1, HIGH);
  digitalWrite(L_CTRL_2, HIGH);
  analogWrite(PWM_L, 0);
}

void RedBotMotor::rightBrake()
{
  digitalWrite(R_CTRL_1, HIGH);
  digitalWrite(R_CTRL_2, HIGH);
  analogWrite(PWM_R, 0);
}

void RedBotMotor::leftStop()
{
  digitalWrite(L_CTRL_1, LOW);
  digitalWrite(L_CTRL_2, LOW);
  analogWrite(PWM_L, 0);
}

void RedBotMotor::rightStop()
{
  digitalWrite(R_CTRL_1, LOW);
  digitalWrite(R_CTRL_2, LOW);
  analogWrite(PWM_R, 0);
}

/******************************************************************************
Private functions for RedBotMotor
******************************************************************************/

void RedBotMotor::leftFwd(byte spd)
{
  digitalWrite(L_CTRL_1, HIGH);
  digitalWrite(L_CTRL_2, LOW);
  analogWrite(PWM_L, spd);
}

void RedBotMotor::leftRev(byte spd)
{
  digitalWrite(L_CTRL_1, LOW);
  digitalWrite(L_CTRL_2, HIGH);
  analogWrite(PWM_L, spd);
}

void RedBotMotor::rightFwd(byte spd)
{
  digitalWrite(R_CTRL_1, HIGH);
  digitalWrite(R_CTRL_2, LOW);
  analogWrite(PWM_R, spd);
}

void RedBotMotor::rightRev(byte spd)
{
  digitalWrite(R_CTRL_1, LOW);
  digitalWrite(R_CTRL_2, HIGH);
  analogWrite(PWM_R, spd);
}

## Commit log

2012-10-30 Initial commit.
2012-11-09 v01 files as sent to protos
2012-12-10 v02 hardware file commit
    Initial protos are messed up- no internal copper layers.
    Took this opportunity to add a couple of new features:
    - .1" headers for input voltage and motor connections
    - PMOS switch to disconnect servos when powered down
    - fixed barrel jack so the right pin is to ground
2012-12-10 Last commit incomplete; this adds header for PS
2012-12-18 Changes from v01 Changed top plane to ground Fixed issue with barrel jack connection Add .1" header for power input by barrel jack Add PMOSFET power switch for servo motors
2013-01-10 Fix a couple of problems: - TEST pin on FTDI chip needs to be grounded. - FTDI chip not properly bypassed.
2013-01-21 Added an AND gate to the reset lines, to improve the multiplexing capabilities of the Xbee/FTDI during bootloads.
2013-02-12 V03 prototypes - Added an AND gate instead of two diodes for reset control - Changed packages on the 5x2 headers along the board edges to be no silk - Moved motor header text to avoid tmask interfere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
2013-05-15 Change board/schematic to v10 - Tweaks to board labels - Change as many 0.015" vias to 0.020" as possible. - Address a few minor clearance issues.
2013-05-15 Moved User LED to pin 13
2013-05-27 Production readied
    add fiducials & create panel
2013-07-02 Fix polarity issue on FT232 LEDs
2013-07-03 Panelized v11 board
2013-07-15 add Arduino files/library
2013-07-24 Update parts to 0603
2013-07-25 Created v12 panel
2013-07-30 Add demo code and update library
2013-07-30 Removed obsolete directory Firmware
2013-08-08 Hardware to v13 - Fix gating of battery voltage to servos - Add a user input button to pin 12 - label user led as D13 LED for clarity
2013-08-08 Add Demo2 sketch.
2013-09-03 Fixing Arduino library structure
2013-10-03 Added support for encoder and whisker bumper; changing schematic and layout to fix some issues and pretty it up a bit. Hardware changes not done!
2013-10-07 Changes to library, changes to board. Will need to do some branching magic to separate the two. This will become the sw dev branch.
2013-10-07 Update boards to v13. - Flip MOSFET to gate power to Servo headers - Add button to pin 12 - change silk on LED to D13 LED - add some silk to the back
2013-10-07 Rollback design to current master
2013-10-08 Added RedBot logo
2013-10-08 Changes to eagle.epf
2013-10-10 Encoder and bumper fixes
2013-11-04 Adding XBee support
2013-11-08 Update to library to include software serial.
2013-11-22 Changed Library_Test for new library changes
2013-11-26 Added PTC to V_GATED
2013-11-26 created panel
2014-01-04 Adds documentation to the RedBot Arduino library.
    Only documentation to the classes public members and methods was
    added as the implementation files are sufficiently documented for
    people who really want to dig.
2014-01-07 Cleaned up readme
2014-01-21 Update library/sketches w/licenses
2014-01-30 Merging library changes for new HW
2014-01-30 Fixed Arudino folder structure
2014-02-06 Add missing files to Arduino library
2014-03-04 Fix infinite loop if no I2C dev present
2014-03-04 Implement timeout for I2C transactions
2014-03-04 Add timeout to all I2C transactions
2014-03-04 FINALLY fixed I2C no-slave issue - Added timeout to each step of the I2C transaction - Learned my lesson about one-line conditional statements
2014-03-15 Added redbot class example code
2014-06-26 Adding in Demo1
2014-07-08 Fixed Demo1 code to use RedBotSoftwareSerial object
2014-07-30 Update README.md
    Fixing licensing.
2014-10-10 PlatformIO Library Manager manifest file
    * This library in Web: http://platformio.ikravets.com/#!/lib/show/Arduino-RedBot
    * Specification: [PlatformIO Library Manager](http://docs.platformio.ikravets.com/en/latest/librarymanager/index.html)
    * Integration: [IDE Integration](http://docs.platformio.ikravets.com/en/latest/ide.html)
    `library.json` is a library manifest file which can be used with different tools/managers to organise embedded libraries. Currently, only [PlatformIO](http://platformio.ikravets.com) uses it. How doe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
    ```bash
    $ platformio lib search “+arduino redbot"
2014-10-23 Move library manifest file to appropriate dir
2014-10-23 PlatformIO Library Manger manifest file
    * This library in Web Registry: http://platformio.ikravets.com/#!/lib/show/60/RedBot
    * Specification: [PlatformIO Library Manager](http://docs.platformio.ikravets.com/en/latest/librarymanager/index.html)
    * Integration: [IDE Integration](http://docs.platformio.ikravets.com/en/latest/ide.html)
2014-12-16 Updated example code and library
    - Updated example / experiment code.
    - Re-named RedBotMotor to RedBotMotors.
    - Added a .coast() method as more appropriately describing
    functionality.
    - Added a .leftMotor() and a .rightMotor() method that allows
    independent control of the right and left motor. Positive values are CW,
2014-12-16 Added Exp9_SerialDrive
    Added 9th example code of using Serial to drive the robot -- makes the
    addition of XBees easier.
2014-12-18 Removed RedBotMotor class
    Re-named RedBotMotor to RedBotMotors. Redundant .cpp file causes the
    library to break.
2014-12-31 Removed extra non-ASCII character in RedBotBumper.cpp file
2015-06-23 Removed desktop.ini files & updated .git files to prevent them from coming back.
2015-06-29 Fix to RedBotMotors::RedBotMotors::leftMotor(int speed, int duration)
    Fixed the direction change in the leftMotor(speed, duration) method.
2015-12-16 created larger v14a panel
2016-02-22 Moving library files into new repository
2016-02-22 Removing unnecessary .git file, updating README with additional product links
2016-02-22 Adding product links to readme
2016-03-03 Squashed 'Libraries/Arduino/' content from commit 88cbdfa
    git-subtree-dir: Libraries/Arduino
    git-subtree-split: 88cbdfa4552ccab708695102eaf8b9ba84870a82
2016-03-03 Adding kit image to README
2016-03-03 Adding library url and README for subtree instructions
2016-03-03 Squashed 'Libraries/Arduino/' changes from 88cbdfa..220f016
    220f016 Adding example 4_2, updating 4_1, 6_1, 6_2, 7_1 meta data
    ee186a0 Updating example 7_3
    git-subtree-dir: Libraries/Arduino
    git-subtree-split: 220f01668567be4ad0f3be12d2eeb6cd0d746865
2016-03-15 Squashed 'Libraries/Arduino/' changes from 220f016..cc6a482
    cc6a482 Adding .json file for PlatformIO
    git-subtree-dir: Libraries/Arduino
    git-subtree-split: cc6a482827ecb4866a96b3ec569d3d5d16813a59
